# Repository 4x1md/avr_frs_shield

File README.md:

# AVR Fuse Rescue Shield for Arduino Uno
AVR Fuse Rescue Shield based on [Arduino-based AVR High Voltage Programmer](http://mightyohm.com/blog/2008/09/arduino-based-avr-high-voltage-programmer/) by Jeff Keyzer W6OHM aka [@mightyohm](https://twitter.com/mightyohm).

## Overview
While working on a new prototype for my [GPS module for Yaesu VX-8DR/DE transceivers](https://github.com/4x1md/vx8_gps), I made some newbie errors burning incorrect fuses into ATmega328P microcontrollers and bricked them. After some research I found [MightyOhm's High Voltage Programmer](http://mightyohm.com/blog/2008/09/arduino-based-avr-high-voltage-programmer/) which could bring them back to life. His programmer was designed as Arduino shield thus I could use the Arduino Uno board I already had. In my project I used MightOhm's schematics with minor changes and his Arduino code as is.

I made this device for recovering ATmega328P chips. It may be compatible with other ATmega's, but you have to check the compatibility before you try. This shield uses high voltage which may damage your microcontroller.

## Schematics
The schematics are almost the same as the original MightyOhm's. Two minor changes are:

1. Zener diode for getting 12V from unregulated power supply.
2. A led connected to microcontrollers Vcc line.

The shield requires external power supply of 12 to 16V. Unregulated power source will work fine.

## PCB Design
The PCB was designed using KiCAD software. As it was meant to be produced at home I designed it as single layer board. There are some front side tracks in the design which were replaced by jumper wires in the real PCB. Toner Transfer method was used to transfer the drawings to copper and front side.

### Copper side
Print version: [avr_frs_pcb.pdf](https://github.com/4x1md/avr_frs_shield/blob/master/printable/avr_frs_pcb.pdf)

### Silk screen
Print version: [avr_frs-silk.pdf](https://github.com/4x1md/avr_frs_shield/blob/master/printable/avr_frs-silk.pdf)

## Software
MightyOhm's original [Arduino code](https://github.com/4x1md/avr_frs_shield/tree/master/avr_frs_arduino) is used without any modifications.

## Alignment
Correctly assembled device requires no alignment.

## How To Use The Device

1. Upload the code to Arduino Uno or compatible board.
2. Connect the shield to the the Arduino.
3. Connect power sources to the Arduino board and to the shield. The red led will light and the green will not.
4. Place the device to recover in the dedicated socket.
5. Press the button on the shield. The green led will light and the red will turn off.
6. Wait until the leds return to their previous states.
7. Enjoy your unbricked microcontroller!

## Photos

## Sources
1. [Arduino-based AVR High Voltage Programmer](http://mightyohm.com/blog/2008/09/arduino-based-avr-high-voltage-programmer/)
2. [Jeff Keller aka @mightyohm's Twitter](https://twitter.com/mightyohm)
3. [Atmel ATmega328P datasheet](http://www.atmel.com/images/atmel-8271-8-bit-avr-microcontroller-atmega48a-48pa-88a-88pa-168a-168pa-328-328p_datasheet_complete.pdf)

## Questions? Suggestions?
You are more than welcome to contact me with any questions, suggestions or propositions regarding this project. You can:

1. Visit [my QRZ.COM page](https://www.qrz.com/db/4X1MD)
2. Visit [my Facebook profile](https://www.facebook.com/Dima.Meln)
3. Write me an email to iosaaris =at= gmail dot com

## How to Support or Say Thanks

If you like this project, or found here some useful information and want to say thanks, or encourage me to do more, you can buy me a coffee!

You can aslo make a donation with PayPal:

---

**73 de 4X1MD**

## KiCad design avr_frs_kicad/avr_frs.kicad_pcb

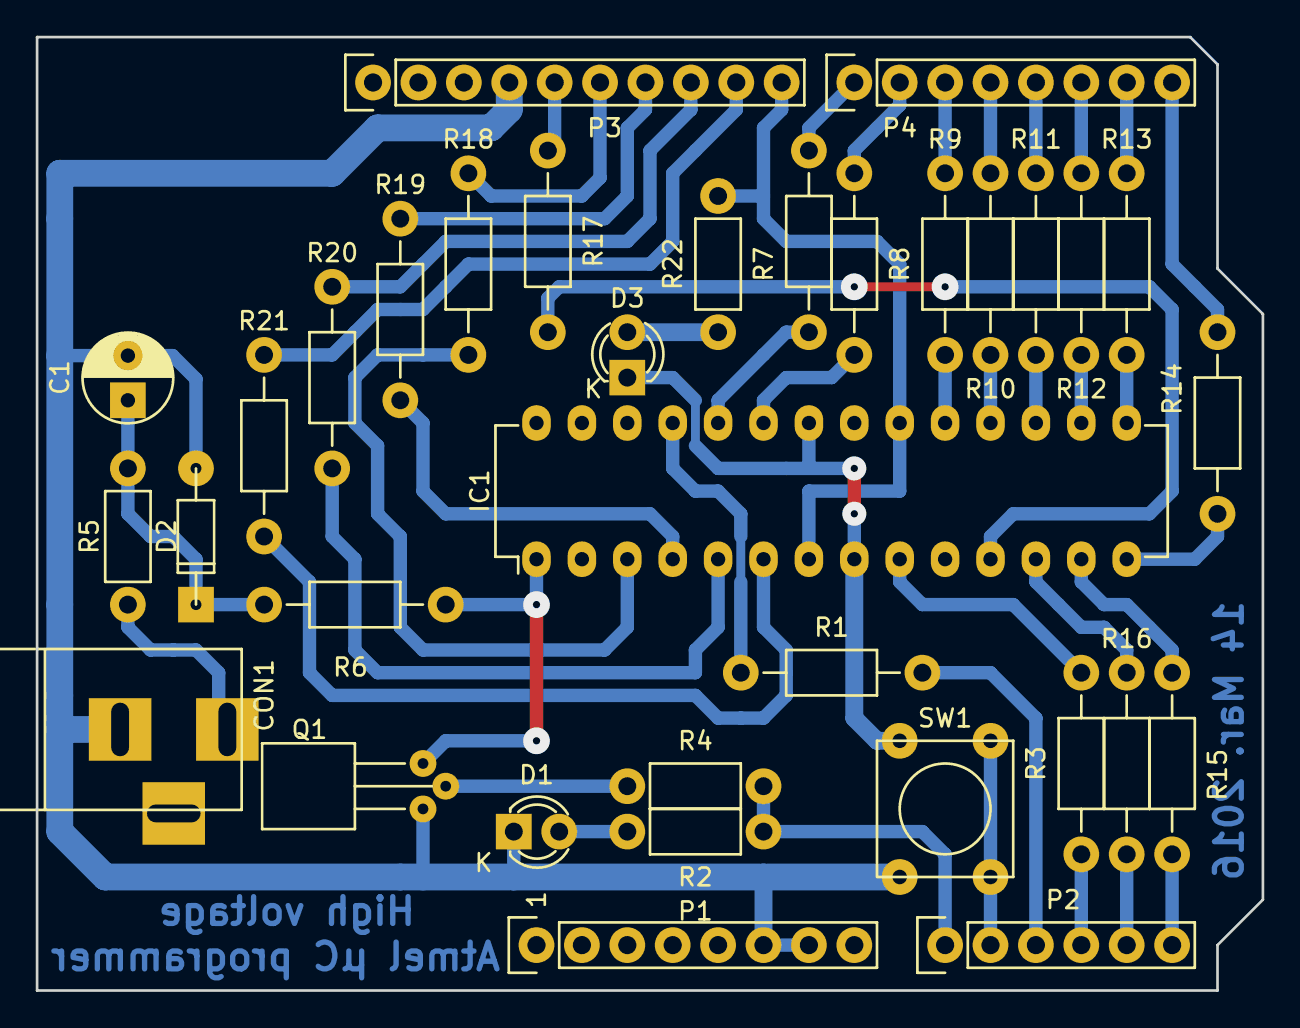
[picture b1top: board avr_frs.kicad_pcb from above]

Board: 2 copper layers, 68.6 x 53.3 mm, 34 parts (0 on the bottom side), 44 nets.

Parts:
C1: 10uF; C_Radial_D5_L6_P2.5
CON1: BARREL_JACK
D1, D3: LED; LED-3MM
D2: 12V; DO-35
IC1: ATMEGA328P-P; DIP-28_W7.62mm
P1: Power; Socket_Strip_Arduino_1x08
P2: Analog; Socket_Strip_Arduino_1x06
P3: Digital; Socket_Strip_Arduino_1x10
P4: Digital; Socket_Strip_Arduino_1x08
Q1: Q_NPN_EBC; TO-92_Horizontal2_Molded_Narrow
R1, R3, R6, R7, R8, R9, R10, R11, R12, R13, R14, R15, R16, R17, R18, R19, R20, R21: 1K; Resistor_Horizontal_RM10mm
R2, R4: 1K; Resistor_Horizontal_RM7mm
R5: 100; Resistor_Horizontal_RM7mm
R22: 390; Resistor_Horizontal_RM7mm
SW1: SW_PUSH; SW_PUSH_SMALL

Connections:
/0(Rx): P4.8, R14.2
/1(Tx): P4.7, R13.2
/2: P4.6, R12.2
/3(**): P4.5, R11.2
/4: P4.4, R10.2
/5(**): P4.3, R9.2
/6(**): P4.2, R8.2
/7: P4.1, R7.2
/8: IC1.7, IC1.20, P3.10, R22.2
/9(**): P3.9, R21.2
/10(**/SS): P3.8, R20.2
/11(**/MOSI): P3.7, R19.2
/12(MISO): P3.6, R18.2
/13(SCK): P3.5, R17.2
/A0: P2.1, R2.1, R4.2
/A1: P2.2, SW1.2
/A2: P2.3, R1.2
/A3: P2.4, R3.2
/A4(SDA): P2.5, R16.2
/A5(SCL): P2.6, R15.2
GNDREF: C1.2, CON1.2, D1.1, D2.2, D3.1, IC1.8, IC1.22, P1.6, P1.7, P3.4, Q1.1, SW1.1
unnamed: C1.1, D2.1, R5.1, R6.2
unnamed: CON1.1, R5.2
unnamed: D1.2, R2.2
unnamed: D3.2, R22.1
unnamed: IC1.1, Q1.3, R6.1
unnamed: IC1.3, R18.1
unnamed: IC1.4, R19.1
unnamed: IC1.5, R20.1
unnamed: IC1.6, R21.1
unnamed: IC1.9, R3.1
unnamed: IC1.11, R17.1
unnamed: IC1.12, R16.1
unnamed: IC1.13, R15.1
unnamed: IC1.14, R14.1
unnamed: IC1.15, R13.1
unnamed: IC1.16, R12.1
unnamed: IC1.17, R11.1
unnamed: IC1.18, R10.1
unnamed: IC1.19, R9.1
unnamed: IC1.23, R8.1
unnamed: IC1.24, R7.1
unnamed: IC1.25, R1.1
unnamed: Q1.2, R4.1

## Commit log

2016-03-18 Arduino code.
2016-03-18 KiCAD circuit & PCB.
2016-03-18 Schematic & 3D models.
2016-03-18 PCB in printable PDF.
2016-03-19 PCB and silk screen in PDF.
2016-03-19 README.md
2016-03-19 Images.
2016-03-19 3D models.
2016-08-05 Removed reference to the library: special.
2016-08-13 Minor rerouting.
2017-09-13 Updated image paths.
